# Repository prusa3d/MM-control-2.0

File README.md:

# PRUSA MM control board

KiCad PCB layout

* [Interactive bom](http://htmlpreview.github.io/?https://github.com/prusa3d/MM-control-2.0/blob/master/rev.03/interactive-BOM.html)
* [STEP 3D model](rev.03/MM-control.step)
* [Firmware](https://github.com/prusa3d/MM-control-01)

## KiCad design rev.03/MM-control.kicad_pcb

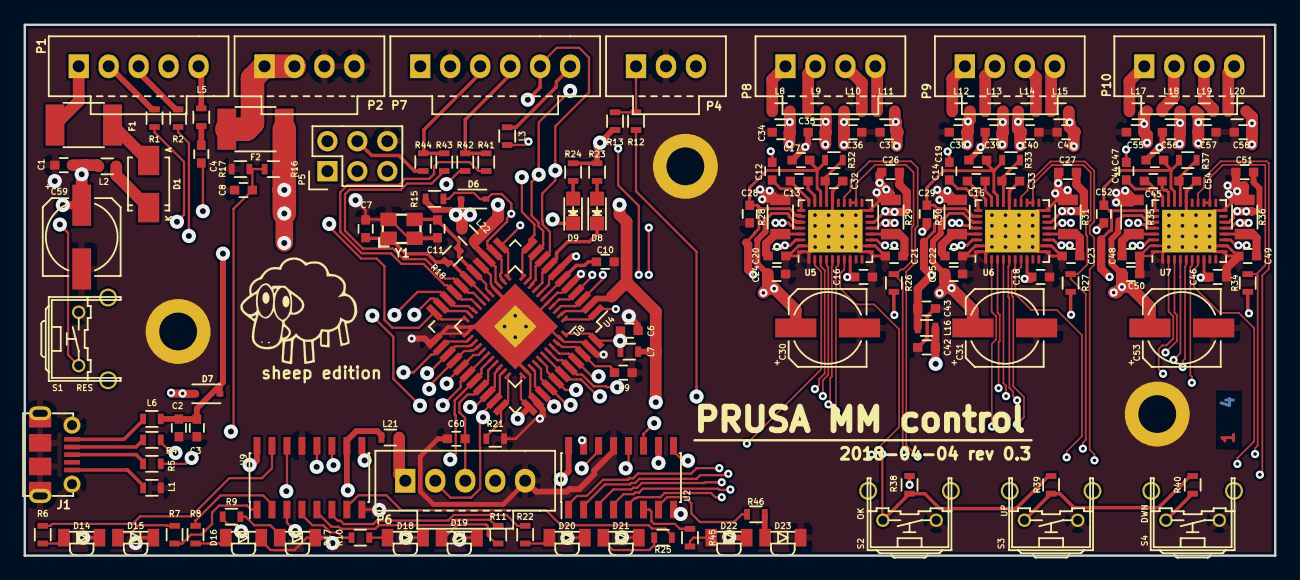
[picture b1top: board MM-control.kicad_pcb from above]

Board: 4 copper layers, 106.0 x 45.0 mm, 164 parts (0 on the bottom side), 131 nets.

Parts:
C1, C2, C4, C8, C9, C12, C14, C16, C17, C18, C19, C20, C21, C22, C23, C24, C25, C26, C27, C28, C29, C42, C44, C46, C47, C48, C49, C50, C51, C52, C60: 100n; C_0603
C3, C43: 10u; C_0603
C6, C10, C32, C33, C54: 1u; C_0603
C7, C11: 22p; C_0603
C13, C15, C45: 22n; C_0603
C30, C31, C53, C59: 100u; c_elec_6.3x7.7
C34, C35, C36, C37, C38, C39, C40, C41, C55, C56, C57, C58: 1n; C_0603
D1: SK310SMA-DIO; SMA_Standard
D6, D7: BAS16HT1G; SOD-323
D8: RX; LED_0805
D9: TX; LED_0805
D14, D16, D18, D20, D22: KPA-3010MGC; LED-1104
D15, D17, D19, D21, D23: KPA-3010SECK; LED-1104
F1: 150mA; R_1812
F2: 750mA; R_1812
J1: MX-105017-0001; USB-micro
L1, L2, L3, L5, L6, L7, L8, L9, L10, L11, L12, L13, L14, L15, L16, L17, L18, L19, L20, L21, L22: FB; R_0603
P1: MOLEX 70543-0004; Pin_1x05-XL
P2, P8, P9, P10: MOLEX 70543-0003; Pin_1x04-XL
P3, P11, P12: MP; MountingHole_3.2mm_M3_ISO14580_Pad
P4: MOLEX 70543-0002; Pin_1x03-XL
P5: ICSP; Pin_Header_Straight_2x03
P6: ShiftOut; Pin_1x05-XL
P7: MOLEX 70543-0004; Pin_1x06-XL
R1, R2, R4, R5: 22R; R_0603
R6, R7, R8, R9, R10, R11, R22, R25, R45, R46: 330R; R_0603
R12: 100R; R_0603
R13, R15, R16, R21, R26, R27, R34: 10k; R_0603
R17, R23, R24: 1k; R_0603
R18: 1M; R_0603
R28, R29, R30, R31, R35, R36: R22; R_1206
R32, R33, R37: 10R; R_0603
R38: 15k; R_0603
R39, R40: 1k5; R_0603
R41, R42, R43, R44: 0R; R_0603
S1: RES; TACT-90
S2: OK; TACT-90
S3: UP; TACT-90
S4: DWN; TACT-90
U2, U9: 74HC595; SOIC-16_3.9x9.9mm_Pitch1.27mm
U4: ATmega32U4; TQFP-44_10x10mm_Pitch0.8mm
U5, U6, U7: TMC2130-LA; QFN-36-1EP_5x6mm_Pitch0.5mm-GNDpad-0.3mm
U8: ATmega32U4; QFN-44-1EP_7x7mm_Pitch0.5mm
Y1: LFXTAL035264BULK 16MHz; Crystal-3.2x2.5mm

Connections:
+5V: C1.1, C42.1, C59.1, D6.1, D7.1, L2.1, L16.1, L21.2, L22.1, P4.3, P5.2, P6.1, P7.1, R13.1, R15.2, R23.1, R24.1, R26.1, R27.1, R34.1, R38.2
+5V-MOT: C16.1, C17.1, C18.1, C19.1, C28.1, C29.1, C43.1, C46.1, C47.1, C52.1, L16.2, R32.1, R33.1, R37.1, U5.8, U5.26, U5.30, U6.8, U6.26, U6.30, U7.8, U7.26, U7.30
+24V: C12.1, C14.1, C24.1, C25.1, C26.1, C27.1, C30.1, C31.1, C44.1, C50.1, C51.1, C53.1, F2.1, R16.1, U5.16, U5.31, U6.16, U6.31, U7.16, U7.31
/D+: R5.2, U4.4, U8.4
/D-: R4.1, U4.3, U8.3
/RESET: C4.2, D6.2, P5.5, R15.1, S1.1, U4.13, U8.13
/VBUS: C2.2, C3.2, D7.2, L6.2, U4.7, U8.7
A0: C8.1, R16.2, R17.1, U4.36, U8.36
A1: R12.2, U4.37, U8.37
A2: R38.1, R39.2, S2.2, U4.38, U8.38
A3: R26.2, U4.39, U5.20, U5.21, U8.39
A4: R27.2, U4.40, U6.20, U6.21, U8.40
A5: R34.2, U4.41, U7.20, U7.21, U8.41
D0(RXD): R1.2, U4.20, U8.20
D1(TXD): R2.2, U4.21, U8.21
D2(SDA): R41.2, U4.19, U8.19
D3(SCL): R43.2, U4.18, U8.18
D4: U4.25, U6.6, U8.25
D5: U4.31, U5.2, U8.31
D6: U4.27, U6.2, U8.27
D7: L3.1, U4.1, U8.1
D8: U4.28, U5.6, U8.28
D9: U2.14, U4.29, U8.29
D10: C60.2, P6.3, U2.12, U4.30, U8.30, U9.12
D11: U4.12, U7.2, U8.12
D12: U4.26, U7.6, U8.26
D13: P6.2, U2.11, U4.32, U8.32, U9.11
DIR-1: U2.15, U5.7
DIR-2: U2.2, U6.7
DIR-3: U2.4, U7.7
EN-1: U2.1, U5.22
EN-2: U2.3, U6.22
EN-3: U2.5, U7.22
GND: C1.2, C2.1, C3.1, C6.1, C7.2, C8.2, C9.1, C10.1, C11.2, C16.2, C17.2, C18.2, C19.2, C20.2, C21.2, C22.2, C23.2, C24.2, C25.2, C26.2, C27.2, C28.2, C29.2, C30.2, C31.2, C32.1, C33.1, C34.1, C35.1, C36.1, C37.1, C38.1, C39.1, C40.1, C41.1, C42.2, C43.2, C46.2, C47.2, C48.2, C49.2, C50.2, C51.2, C52.2, C53.2, C54.1, C55.1, C56.1, C57.1, C58.1, C59.2, C60.1, D14.1, D15.1, D16.1, D17.1, D18.1, D19.1, D20.1, D21.1, D22.1, D23.1, J1.6, L1.1, P2.3, P2.4, P3.1, P4.2, P5.6, P6.5, P7.2, P11.1, P12.1, R17.2, R21.2, R28.1, R29.1, R30.1, R31.1, R35.1, R36.1, S1.2, S2.1, S3.1, S4.1, U2.8, U2.13, U4.5, U4.15, U4.23, U4.35, U4.43, U5.1, U5.11, U5.12, U5.18, U5.24, U5.35, U5.36, U5.37, U6.1, U6.11, U6.12, U6.18, U6.24, U6.35, U6.36, U6.37, U7.1, U7.11, U7.12, U7.18, U7.24, U7.35, U7.36, U7.37, U8.5, U8.15, U8.23, U8.35, U8.43, U9.8, U9.13, Y1.2, Y1.4
MISO: P5.1, R42.2, U4.11, U5.5, U6.5, U7.5, U8.11
MOSI: P5.4, R44.2, U4.10, U5.4, U6.4, U7.4, U8.10
unnamed: C4.1, L5.1
unnamed: C6.2, L7.1, U4.24, U4.44, U8.24, U8.44
unnamed: C7.1, R18.2, U4.17, U8.17, Y1.1
unnamed: C9.2, U4.42, U8.42
unnamed: C10.2, U4.6, U8.6
unnamed: C11.1, R18.1, U4.16, U8.16, Y1.3
unnamed: C12.2, U5.29
unnamed: C13.1, U5.27
unnamed: C13.2, U5.28
unnamed: C14.2, U6.29
unnamed: C15.1, U6.27
unnamed: C15.2, U6.28
unnamed: C20.1, R28.2, U5.33
unnamed: C21.1, R29.2, U5.14
unnamed: C22.1, R30.2, U6.33
unnamed: C23.1, R31.2, U6.14
unnamed: C32.2, R32.2, U5.25
unnamed: C33.2, R33.2, U6.25
unnamed: C34.2, L8.1, U5.32
unnamed: C35.2, L9.1, U5.34
unnamed: C36.2, L10.1, U5.15
unnamed: C37.2, L11.1, U5.13
unnamed: C38.2, L12.1, U6.32
unnamed: C39.2, L13.1, U6.34
unnamed: C40.2, L14.1, U6.15
unnamed: C41.2, L15.1, U6.13
unnamed: C44.2, U7.29
unnamed: C45.1, U7.27
unnamed: C45.2, U7.28
unnamed: C48.1, R35.2, U7.33
unnamed: C49.1, R36.2, U7.14
unnamed: C54.2, R37.2, U7.25
unnamed: C55.2, L17.1, U7.32
unnamed: C56.2, L18.1, U7.34
unnamed: C57.2, L19.1, U7.15
unnamed: C58.2, L20.1, U7.13
unnamed: D1.1, L2.2
unnamed: D1.2, F1.2
unnamed: D8.1, U4.8, U8.8
unnamed: D8.2, R23.2
unnamed: D9.1, U4.22, U8.22
unnamed: D9.2, R24.2
unnamed: D14.2, R6.2
unnamed: D15.2, R7.2
unnamed: D16.2, R8.2
unnamed: D17.2, R9.2
unnamed: D18.2, R10.2
unnamed: D19.2, R11.2
unnamed: D20.2, R22.2
unnamed: D21.2, R25.2
unnamed: D22.2, R45.2
unnamed: D23.2, R46.2
unnamed: F1.1, P1.1
unnamed: F2.2, P2.1, P2.2
unnamed: J1.1, L6.1
unnamed: J1.2, R4.2
unnamed: J1.3, R5.1
unnamed: J1.5, L1.2
unnamed: L3.2, P7.6
unnamed: L5.2, P1.5
unnamed: L8.2, P8.1
unnamed: L9.2, P8.2
unnamed: L10.2, P8.3
unnamed: L11.2, P8.4
unnamed: L12.2, P9.1
unnamed: L13.2, P9.2
unnamed: L14.2, P9.3
unnamed: L15.2, P9.4
unnamed: L17.2, P10.1
unnamed: L18.2, P10.2
unnamed: L19.2, P10.3
unnamed: L20.2, P10.4
unnamed: L21.1, U2.10, U2.16, U9.10, U9.16
unnamed: L7.2, L22.2, U4.2, U4.14, U4.34, U8.2, U8.14, U8.34
unnamed: P1.2, R1.1
unnamed: P1.3, R2.1
unnamed: P4.1, R12.1, R13.2
unnamed: P6.4, U9.9
unnamed: P7.3, R43.1, R44.1
unnamed: P7.4, R41.1, R42.1
unnamed: R6.1, U9.15
unnamed: R7.1, U9.1
unnamed: R8.1, U9.2
unnamed: R9.1, U9.3
unnamed: R10.1, U9.4
unnamed: R11.1, U9.5
unnamed: R21.1, U4.33, U8.33
unnamed: R22.1, U9.6
unnamed: R25.1, U9.7
unnamed: R39.1, R40.2, S3.2
unnamed: R40.1, S4.2
unnamed: R45.1, U2.6
unnamed: R46.1, U2.7
unnamed: U2.9, U9.14
SCK: P5.3, P7.5, U4.9, U5.3, U6.3, U7.3, U8.9

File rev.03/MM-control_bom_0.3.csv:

Component,Description,Part,References,Value,Footprint,Quantity Per PCB,Req
1,Unpolarized capacitor,C,C1 C2 C4 C9 C12 C14 C16 C17 C18 C19 C20 C21 C22 C23 C24 C25 C26 C27 C28 C29 C42 C44 C46 C47 C48 C49 C50 C51 C52 C60,100n,C_0603,30,50V/X7R/10%
2,,Csmall,C8,100n,C_0603,1,50V/X7R/10%
3,Polarised capacitor,CP_Small,C30 C31 C53 C59,100u,c_elec_6.3x7.7,4,35V/20%
4,Unpolarized capacitor,C,C3,10u,C_0603,1,"6,3V/X5R/20%"
5,Polarised capacitor,CP_Small,C43,10u,C_0603,1,"6,3V/X5R/20%"
6,Unpolarized capacitor,C_Small,C34 C35 C36 C37 C38 C39 C40 C41 C55 C56 C57 C58,1n,C_0603,12,50V/X7R/10%
7,Unpolarized capacitor,C,C6 C10 C32 C33 C54,1u,C_0603,5,"6,3V/X5R/10%"
8,Unpolarized capacitor,C_Small,C13 C15 C45,22n,C_0603,3,50V/X7R/10%
9,,Csmall,C7 C11,22p,C_0603,2,50V/C0G/10%
10,"Diode, alternativ symbol",D_ALT,D6 D7,BAS16HT1G,SOD-323,2,
11,"LED, small symbol, alternativ symbol",LED_Small_ALT,D14 D16 D18 D20 D22,KPA-3010MGC,LED-1104,5,
12,"LED, small symbol, alternativ symbol",LED_Small_ALT,D15 D17 D19 D21 D23,KPA-3010SECK,LED-1104,5,
13,"LED generic, alternativ symbol",LED_ALT,D8,RX,LED_0805,1,
14,"Diode, alternativ symbol",D_ALT,D1,SK310SMA-DIO,SMA_Standard,1,
15,"LED generic, alternativ symbol",LED_ALT,D9,TX,LED_0805,1,
16,"resettable fuse, polymeric positive temperature coefficient (PPTC), small symbol",Polyfuse_Small,F1,150mA,R_1812,1,
17,"resettable fuse, polymeric positive temperature coefficient (PPTC), small symbol",Polyfuse_Small,F2,750mA,R_1812,1,
18,,USB-micro,J1,MX-105017-0001,USB-micro,1,
19,"Inductor with ferrite core, small symbol",L_Core_Ferrite_Small,L1 L2 L3 L5 L6 L7 L8 L9 L10 L11 L12 L13 L14 L15 L16 L17 L18 L19 L20 L21 L22,FB BLM18KG121TN1D,R_0603,21,
20,,CONN_3X2,P5,ICSP,Pin_Header_Straight_2x03,1,
21,"Connector, single row, 01x03",CONN_01X03,P4,MOLEX 70543-0002,Pin_1x03-XL,1,
22,"Connector, single row, 01x04",CONN_01X04,P8 P9 P10,MOLEX 70543-0003,Pin_1x04-XL,3,
23,"Connector, double row, 02x02",CONN_02X02,P2,MOLEX 70543-0003,Pin_1x04-XL,1,
24,"Connector, single row, 01x06",CONN_01X06,P7,MOLEX 70543-0004,Pin_1x06-XL,1,
25,"Connector, single row, 01x05",CONN_01X05,P1,MOLEX 70543-0004 ,Pin_1x05-XL,1,
26,"Connector, single row, 01x05",CONN_01X05,P6,ShiftOut,Pin_1x05-XL,1,
27,Resistor,R,R41 R42 R43 R44,0R,R_0603,4,"0,1W/5%"
28,Resistor,R,R12,100R,R_0603,1,"0,1W/1%"
29,Resistor,R,R32 R33 R37,10R,R_0603,3,"0,1W/1%"
30,Resistor,R,R13 R15 R16 R21 R26 R27 R34,10k,R_0603,7,"0,1W/1%"
31,Resistor,R,R38,15k,R_0603,1,"0,1W/1%"
32,Resistor,R,R18,1M,R_0603,1,"0,1W/1%"
33,Resistor,R,R17 R23 R24,1k,R_0603,3,"0,1W/1%"
34,Resistor,R,R39 R40,1k5,R_0603,2,"0,1W/1%"
35,Resistor,R,R1 R2 R4 R5,22R,R_0603,4,"0,1W/1%"
36,Resistor,R,R6 R7 R8 R9 R10 R11 R22 R25 R45 R46,330R,R_0603,10,"0,1W/1%"
37,Resistor,R,R28 R29 R30 R31 R35 R36,R22,R_1206,6,"0,5W/1%"
38,,TACT-SW2,S4,DWN,TACT-90,1,
39,,TACT-SW2,S2,OK,TACT-90,1,
40,,TACT-SW2,S1,RES,TACT-90,1,
41,,TACT-SW2,S3,UP,TACT-90,1,
42,,74HC595,U2 U9,74HC595,SOIC-16_3.9x9.9mm_Pitch1.27mm,2,
43,,ATmega32U4,U4,ATmega32U4,TQFP-44_10x10mm_Pitch0.8mm,1,
44,,ATmega32U4,U8,ATmega32U4,QFN-44-1EP_7x7mm_Pitch0.5mm,1,
45,,TCM2130-LA,U5 U6 U7,TMC2130-LA,QFN-36-1EP_5x6mm_Pitch0.5mm-GNDpad-0.3mm,3,
46,"Four pin crystal (GND on pins 2 and 4), e.g. in SMD package",Crystal_GND24,Y1,LFXTAL035264BULK 16MHz,Crystal-3.2x2.5mm,1,
,,,,,,,
,,,,,,,
,,,,,,,
,,,,,,,
,,,,,,,
Component Groups:,46,,,,,,
Component Count:,161,,,,,,
Fitted Components:,161,,,,,,
Number of PCBs:,1,,,,,,
Total components:,161,,,,,,
Schematic Version:,0.3,,,,,,

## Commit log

2018-08-30 rev.03
2018-08-30 readme fix
